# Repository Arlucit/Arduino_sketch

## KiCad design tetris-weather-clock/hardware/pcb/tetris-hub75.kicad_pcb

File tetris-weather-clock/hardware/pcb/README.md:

# Scheda ESP32 → HUB75 (singolo pannello, senza componenti extra)

Scheda 76,2 × 57,15 mm, 2 strati. Montati ci sono solo: due strip femmina 1x19 per la DevKit a 38 pin, un header HUB75 2x8 e due morsetti a vite a 5 V. Nessun chip, condensatore, fusibile o diodo.

- I segnali vanno **direttamente** dai GPIO ai pin HUB75 (R1=25 G1=26 B1=27 R2=14 G2=12 B2=13 A=23 B=19 C=5 D=17 E=18 CLK=16 LAT=4 OE=15).
- Il 5 V dal morsetto "5V IN" alimenta sia il pin 5V dell'ESP sia il morsetto "5V PANNELLO". Non collegare il USB dell'ESP mentre e' alimentato dal morsetto, salvo sapere che la DevKit ha il diodo di protezione.
- Il fotoresistore (IO35) non e' sulla scheda: va collegato a parte.
- `tetris-hub75-gerber.zip` per la produzione, `tetris-hub75.kicad_pcb` (non provato in KiCad), `BOM.csv`, `netlist.csv`, anteprime, `gen_pcb.py` (generatore).
- `gen_pcb_con_buffer.py`: variante precedente con 2x 74HCT245, USB-C, PTC, diodo, condensatori (per quando servira').

Da verificare prima di ordinare: piedinatura della propria DevKit (liste `Lp`/`Rp`), pin 1 dell'HUB75, DRC in KiCad. Controlli interni passati: nessun corto, nessun aperto, distanze >= 0,2 mm.

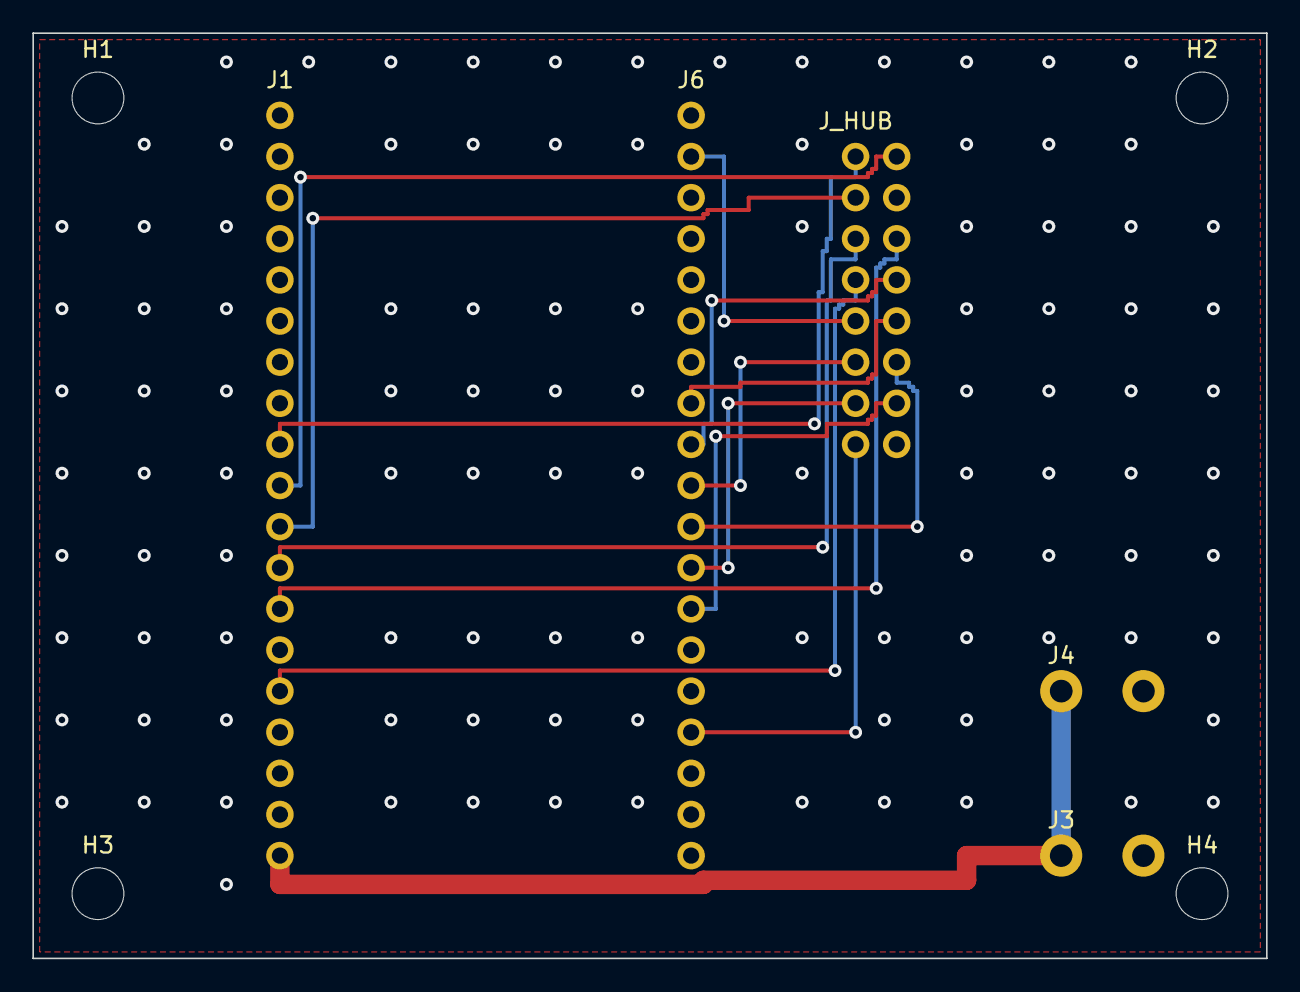
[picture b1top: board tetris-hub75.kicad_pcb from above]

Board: 2 copper layers, 76.2 x 57.1 mm, 9 parts (0 on the bottom side), 16 nets.

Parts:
H1, H2, H3, H4: MountingHole_3.2mm_M3
J1: ESP32 DevKit sx; Socket_1x19_P2.54
J3: Ingresso 5V; TerminalBlock_5.08_1x2
J4: Alim. pannello; TerminalBlock_5.08_1x2
J6: ESP32 DevKit dx; Socket_1x19_P2.54
J_HUB: HUB75 2x8; IDC-Header_2x08_P2.54_Vertical

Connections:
+5V: J1.19, J3.1, J4.1
A_H: J6.2, J_HUB.9
B1_H: J1.11, J_HUB.3
B2_H: J1.15, J_HUB.7
B_H: J6.8, J_HUB.10
CLK_H: J6.12, J_HUB.13
C_H: J6.10, J_HUB.11
D_H: J6.11, J_HUB.12
E_H: J6.9, J_HUB.8
G1_H: J1.10, J_HUB.2
G2_H: J1.13, J_HUB.6
GND: J1.14, J3.2, J4.2, J6.1, J6.7, J_HUB.4, J_HUB.16
LAT_H: J6.13, J_HUB.14
OE_H: J6.16, J_HUB.15
R1_H: J1.9, J_HUB.1
R2_H: J1.12, J_HUB.5

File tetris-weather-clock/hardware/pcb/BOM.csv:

Rif,Valore,Footprint,Q.ta,Note
J1,ESP32 DevKit sx,Socket_1x19_P2.54,1,"femmina 1x19, lato sx"
J6,ESP32 DevKit dx,Socket_1x19_P2.54,1,"femmina 1x19, lato dx"
J_HUB,HUB75 2x8,IDC-Header_2x08_P2.54_Vertical,1,header box 2x8 per il flat del pannello
J3,Ingresso 5V,TerminalBlock_5.08_1x2,1,"morsetto: 5V dall'alimentatore, alimenta ESP e pannello"
J4,Alim. pannello,TerminalBlock_5.08_1x2,1,morsetto: cavo di alimentazione del pannello
